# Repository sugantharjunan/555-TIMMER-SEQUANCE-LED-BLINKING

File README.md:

# 555 Timer Sequence LED Blinking Circuit – KiCad PCB Design

A simple and efficient **555 Timer Sequence LED Blinking Circuit** designed using **KiCad EDA**. This project uses the **NE555 Timer IC** and **CD4017 Decade Counter IC** to create a sequential LED blinking pattern.

The circuit is ideal for beginners learning electronics, PCB design, digital logic, and timer-based applications.

---

# Project Overview

This project demonstrates:

* 555 Timer astable oscillator design
* Sequential LED blinking using CD4017
* PCB design in KiCad
* Through-hole component placement
* LED pattern generation
* 3D PCB visualization

---

# Features

* Sequential LED blinking effect
* Adjustable blinking speed
* Compact PCB layout
* Easy-to-build circuit
* Beginner-friendly electronics project
* Through-hole components
* Designed using KiCad

---

# Software Used

* KiCad

Official Website: [KiCad Official Website](https://www.kicad.org?utm_source=chatgpt.com)

---

# Hardware Components

| Component      | Description         |
| -------------- | ------------------- |
| NE555          | Timer IC            |
| CD4017         | Decade Counter IC   |
| LEDs           | Output indicators   |
| Resistors      | Current limiting    |
| Capacitor      | Timing capacitor    |
| Screw Terminal | Power input         |
| IC Holders     | DIP socket mounting |

---

# Project Structure

```bash id="b4vwk5"
555-TIMER-SEQUENCE-LED/
│
├── Schematic/
│   └── 555_sequence_led.kicad_sch
│
├── PCB/
│   └── 555_sequence_led.kicad_pcb
│
├── Gerber/
│   └── Manufacturing_Files
│
├── Images/
│   ├── 555_TIMER_3D_FRONT.png
│   ├── 555_TIMER_3D_BACK.png
│   ├── 555_TIMER_PCB.png
│   └── 555_TIMER_SCHEMATIC.png
│
└── README.md
```

---

# Circuit Description

The circuit uses a **555 Timer IC** configured in astable mode to generate clock pulses.

These clock pulses are supplied to the **CD4017 Decade Counter**, which activates LEDs sequentially one after another.

---

# Working Principle

1. The NE555 generates continuous clock pulses.
2. CD4017 receives the clock signal.
3. Each output pin of CD4017 turns ON sequentially.
4. LEDs connected to outputs blink in sequence.
5. Timing components control blinking speed.

---

# PCB Design

The PCB was designed with:

* Clean trace routing
* Proper component spacing
* Through-hole assembly
* Compact board size
* Easy soldering access
* Organized LED placement

---

# Electrical Specifications

| Parameter         | Value                   |
| ----------------- | ----------------------- |
| Operating Voltage | 9V – 12V DC             |
| Timer IC          | NE555                   |
| Counter IC        | CD4017                  |
| Output Type       | Sequential LED Blinking |
| PCB Tool          | KiCad                   |

---

# Applications

* LED Chaser Projects
* Decorative Lighting
* Electronics Learning
* Timing Circuits
* Embedded Electronics Practice
* Signal Sequencing Projects

---

# Blinking Speed Control

The blinking speed depends on:

* Timing resistor values
* Capacitor value connected to NE555

You can modify these components to change the LED sequence speed.

---

# Future Improvements

* Add variable speed potentiometer
* Add more LED channels
* Add sound synchronization
* Add RGB LED support
* Convert to SMD version

---

This project is open-source and available under the MIT License.

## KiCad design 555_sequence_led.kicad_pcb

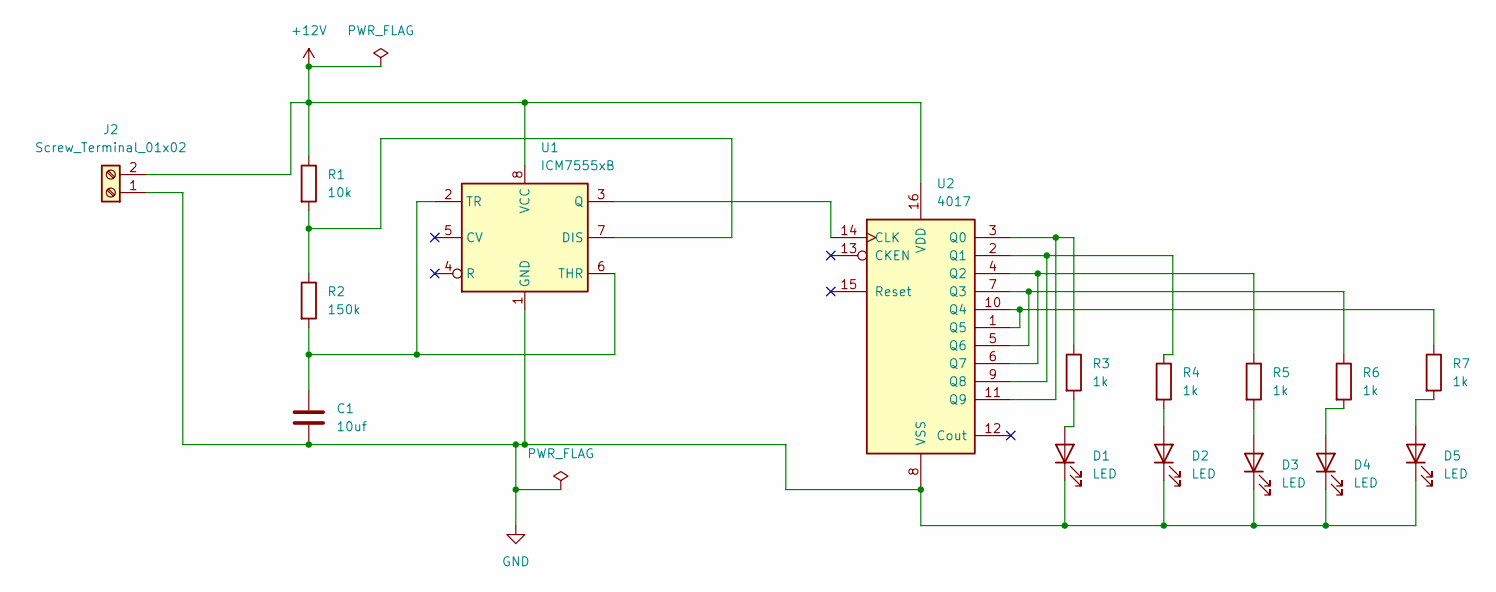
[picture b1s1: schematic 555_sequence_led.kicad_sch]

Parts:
C1: 10uf; CP_Radial_D5.0mm_P2.00mm
D1, D2, D3, D4, D5: LED; LED_D3.0mm
J2: Screw_Terminal_01x02; TerminalBlock_Phoenix_MKDS-1,5-2-5.08_1x02_P5.08mm_Horizont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
R1: 10k; R_Axial_DIN0207_L6.3mm_D2.5mm_P7.62mm_Horizontal
R2: 150k; R_Axial_DIN0207_L6.3mm_D2.5mm_P7.62mm_Horizontal
R3, R4, R5, R6, R7: 1k; R_Axial_DIN0207_L6.3mm_D2.5mm_P7.62mm_Horizontal
U1: ICM7555xB; DIP-8_W7.62mm_Socket
U2: 4017; DIP-16_W7.62mm_Socket

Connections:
+12V: J2.2, R1.1, U1.8 (VCC), U2.16 (VDD)
GND: C1.2, D1.1 (K), D2.1 (K), D3.1 (K), D4.1 (K), D5.1 (K), J2.1, U1.1 (GND), U2.8 (VSS)
unnamed: D1.2 (A), R3.2
unnamed: D2.2 (A), R4.2
unnamed: D3.2 (A), R5.2
unnamed: D4.2 (A), R6.2
unnamed: D5.2 (A), R7.2
unnamed: R1.2, R2.1, U1.7 (DIS)
unnamed: U1.3 (Q), U2.14 (CLK)
unnamed: C1.1, R2.2, U1.2 (TR), U1.6 (THR)
unnamed: R3.1, U2.3 (Q0), U2.11 (Q9)
unnamed: R4.1, U2.2 (Q1), U2.9 (Q8)
unnamed: R5.1, U2.4 (Q2), U2.6 (Q7)
unnamed: R6.1, U2.5 (Q6), U2.7 (Q3)
unnamed: R7.1, U2.1 (Q5), U2.10 (Q4)

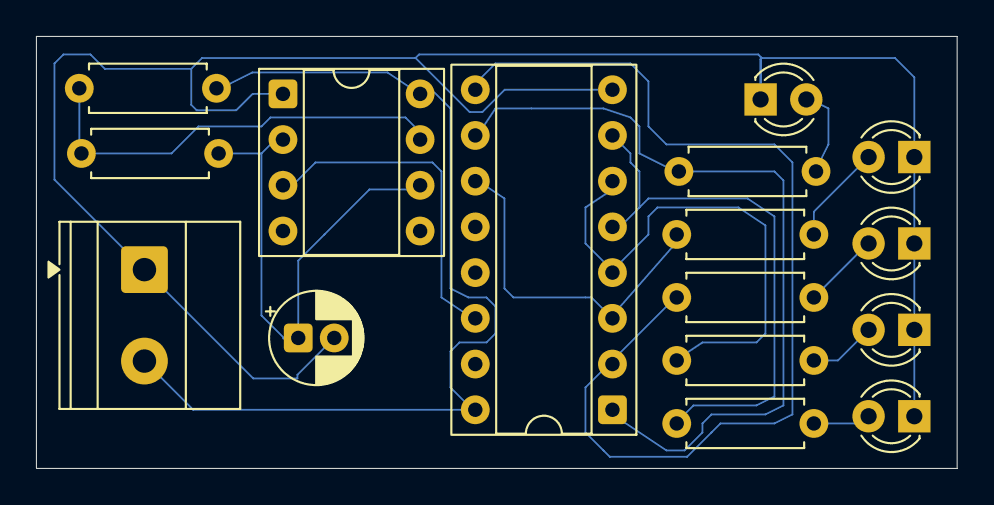
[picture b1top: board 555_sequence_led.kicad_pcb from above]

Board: 2 copper layers, 51.2 x 24.0 mm, 16 parts (0 on the bottom side), 15 nets.

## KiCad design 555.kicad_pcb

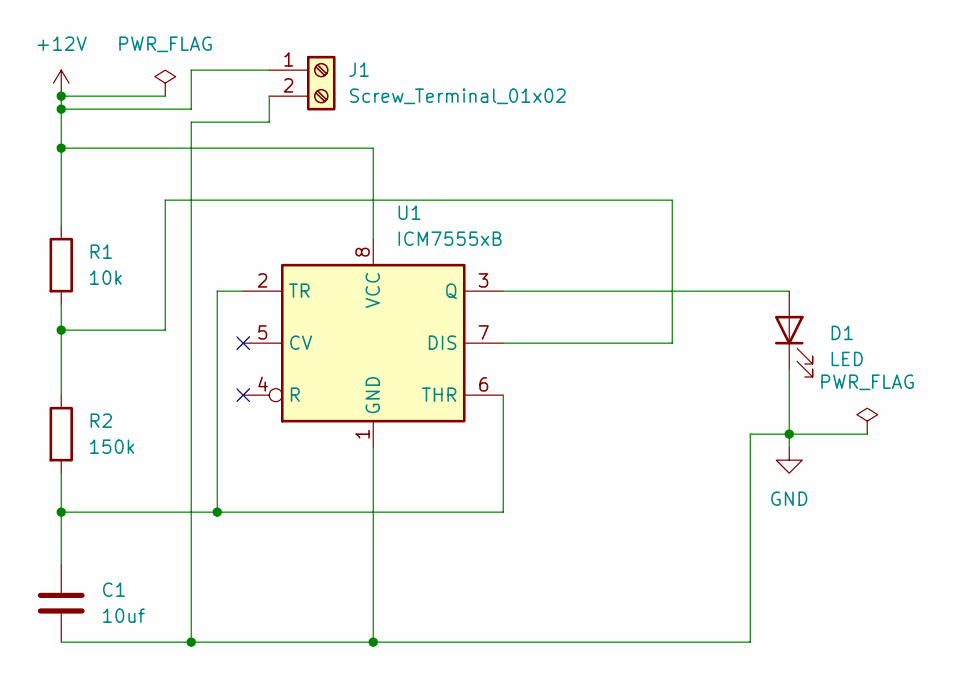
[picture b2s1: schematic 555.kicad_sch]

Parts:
C1: 10uf; CP_Radial_D5.0mm_P2.00mm
D1: LED; LED_D3.0mm
J1: Screw_Terminal_01x02; TerminalBlock_Phoenix_MKDS-1,5-2-5.08_1x02_P5.08mm_Horizont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
R1: 10k; R_Axial_DIN0207_L6.3mm_D2.5mm_P7.62mm_Horizontal
R2: 150k; R_Axial_DIN0207_L6.3mm_D2.5mm_P7.62mm_Horizontal
U1: ICM7555xB; DIP-8_W7.62mm_Socket_LongPads

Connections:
+12V: J1.1, R1.1, U1.8 (VCC)
GND: C1.2, D1.1 (K), J1.2, U1.1 (GND)
unnamed: D1.2 (A), U1.3 (Q)
unnamed: R1.2, R2.1, U1.7 (DIS)
unnamed: C1.1, R2.2, U1.2 (TR), U1.6 (THR)

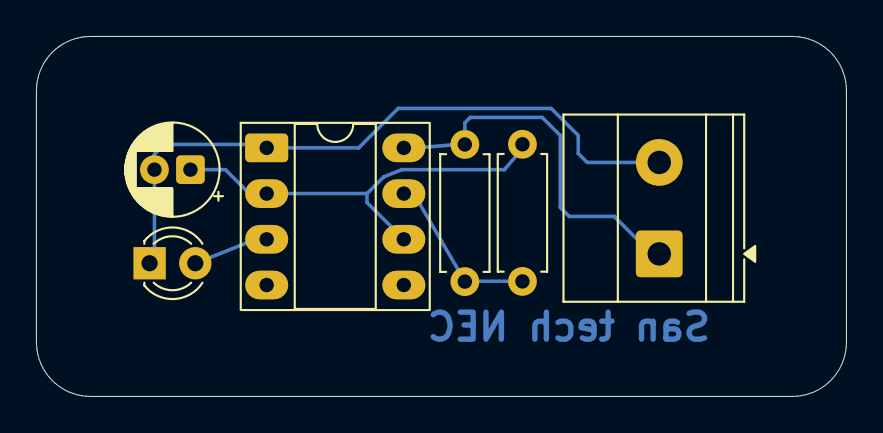
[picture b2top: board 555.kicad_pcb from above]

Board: 2 copper layers, 45.0 x 20.0 mm, 6 parts (0 on the bottom side), 5 nets.
